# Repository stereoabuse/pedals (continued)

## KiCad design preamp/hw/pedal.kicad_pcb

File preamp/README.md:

# preamp

High-gain preamp pedal by stereoabuse. Derived from the Friedman BE-OD circuit (via the public PedalPCB "Thermionic Distortion" schematic), reworked for downtuned rhythm playing and for driving a power-amp input.

This is the single-section version: the boost is built into the preamp's first stage and only works while the preamp is on. The sibling design with a standalone boost is in [../boost-preamp](../boost-preamp). Commands below are run from inside this folder. Untested hardware: the circuit is simulated and the board passes KiCad DRC, but no board has been built yet.

## What it is

| Control | Type | Notes |
|---|---|---|
| Gain | A1M pot | Audio taper, so the sweep is more usable than the stock linear pot |
| Tight | C100K pot | Bass cut before the gain stages, about 75 Hz to 1.7 kHz |
| Presence | C10K pot | Stock BE-OD presence |
| Treble | B100K pot | Stock |
| Mid | B100K pot | New. About +/-13 dB centred near 750 Hz |
| Volume | A10K pot | Low output impedance for power-amp inputs |
| Depth | SPDT on-off-on | Post-distortion low thump: flat, +6 dB, +10 dB around 90 Hz |
| Clip | SPDT on-off-on | Stock soft clip, none (open), single diode pair (saturated) |
| Bypass | 3PDT footswitch | True bypass |
| Boost | 3PDT footswitch | TS-style tightening boost into the first stage, up to +12 dB above 700 Hz |

Inside: gain trim (stock), boost level trim, noise gate threshold trim, and two solder jumpers (18 V or 9 V rail, gate on or off).

Differences from the BE-OD: no Bass knob (Tight and Depth cover it), added Mid, boost, noise gate, clip switch, and an internal charge pump that runs the op-amps at about 16 V from a 9 V supply or battery.

## Ordering from JLCPCB

Files are in [fab/](fab/).

1. Upload `preamp-revA-gerbers.zip`. Settings: 4 layers, 1.6 mm, 82 x 62.5 mm. Layer order is F, In1, In2, B (`.gtl`, `.g1`, `.g2`, `.gbl`).
2. Turn on PCB Assembly, top side.
3. Upload `preamp-revA-bom.csv` and `preamp-revA-cpl.csv`.
4. In the placement preview, check pin 1 on U1 to U6, the two JFETs (Q1, Q2), the diode cathode bars, and the stripe on C20, C27, C28. JLC's rotation convention differs from KiCad's for some packages; the CPL already applies the usual corrections, but this is the step to catch a mistake.

38 BOM lines, 120 placements. 7 of the lines are JLC "extended" parts (a small one-time fee each). Stock was checked on 2026-11-11.

## Parts you solder

| Part | Qty | Notes |
|---|---|---|
| Alpha 16 mm right-angle PCB pot (RV16AF-41) | 6 | A1M, C100K, C10K, B100K x2, A10K |
| Mini toggle, SPDT on-off-on | 2 | Solder lug or PC pin, 4.7 mm lug pitch |
| 3PDT footswitch | 2 | Wired, not board mounted |
| 3 mm LED | 2 | Any colour |
| 1/4" jack | 2 | Input must be stereo (battery switching) |
| 2.1 mm DC jack with switch lug | 1 | Panel mount, insulated |
| 9V battery snap | 1 | |
| Hammond 1590BB enclosure | 1 | |

Pots, toggles and LEDs mount on the back of the board (the side with the pot outlines). Fit them loosely, bolt everything into the drilled enclosure, then solder, so the heights settle correctly.

Drill template (front view, 1:1): [docs/drill-template-1590BB.svg](docs/drill-template-1590BB.svg). Hole positions in mm from the face centre:

| Hole | x | y | dia |
|---|---|---|---|
| Volume | -31.5 | +23.0 | 7.5 |
| Treble | -10.5 | +23.0 | 7.5 |
| Presence | +10.5 | +23.0 | 7.5 |
| Gain | +31.5 | +23.0 | 7.5 |
| Depth | -8.0 | +1.5 | 6.5 |
| Clip | +8.0 | +1.5 | 6.5 |
| Mid | -31.5 | -8.0 | 7.5 |
| Tight | +31.5 | -8.0 | 7.5 |
| Boost LED | -19.5 | -24.0 | 3.2 |
| Bypass LED | +19.5 | -24.0 | 3.2 |
| Boost switch | -27.0 | -43.0 | 12.5 |
| Bypass switch | +27.0 | -43.0 | 12.5 |

The toggles sit sideways (levers move left and right). The battery lies between the footswitches in the board's notch. That fit is snug: check it with a real battery before drilling.

## Wiring

The diagram ([SVG](docs/wiring.svg)) shows every off-board wire. The tables below list the same connections lug by lug.

Pads are labelled on the SMD side. Looking at the SMD side, the left leg (IN, G, L1) is next to the bypass switch.

Bypass switch (3PDT, columns A B C, row 2 is the common):

| Lug | Goes to |
|---|---|
| A1 | board IN |
| A2 | input jack tip |
| A3 | wire to B3 |
| B1 | board OUT |
| B2 | output jack tip |
| C1 | board L1 (left leg) |
| C2 | board G |
| C3 | board IN (grounds the input when bypassed) |

Boost switch:

| Lug | Goes to |
|---|---|
| A2 | board BST |
| A3 | board G |
| B1 | board L1 (right leg) |
| B2 | board L2 |

The boost is on when BST is left open and off when BST is grounded. Wired as above, the boost LED only lights when the pedal is engaged.

Power: DC jack centre pin to G, DC jack sleeve to +9V, battery red to the DC jack switch lug, battery black to the input jack ring lug, input jack sleeve to G.

Use a regulated 9 V centre-negative supply only. The charge pump chip is rated to 12 V, and there is no over-voltage clamp.

## Setting the trimmers

- GAIN TRIM: sets how hard the last gain stage is driven. Start at halfway.
- BST LVL: boost amount and voicing. One end is a tight mid/treble push (+12 dB above 700 Hz), the other a very mild full-range lift (+1 dB). Most of the useful range is in the first quarter of the turn.
- GATE: threshold. Turn until hiss cuts off when you mute the strings but sustained notes do not chop.

Toggle positions as designed (seen from the front): Clip lever left is stock, centre is open, right is saturated. Depth lever left is medium, centre is flat, right is deep. If a switch you buy works the other way round, turn it 180 degrees.

## If something misbehaves

- Gate causes trouble: cut the GATE solder jumper. The gate is then out of circuit.
- Whine from the charge pump: cut the 18V side of the 18V/9V jumper and bridge the 9V side. If you run on the 9 V rail, also cut the GATE jumper, because the gate needs the higher rail to switch cleanly.
- Test pads: VCC should read about 16 V, VREF about half that, 9V about 8.7 V.

## How the board was made

Everything is generated from [hw/design.py](hw/design.py), which holds the full netlist with JLC part numbers.

## Schematic

[docs/schematic.pdf](docs/schematic.pdf), five sheets. It is drawn by `hw/schematic.py`, which extracts the connectivity of the drawing and refuses to write it unless every pin matches the board netlist, so the drawing and the board cannot drift apart. It is a drawing, not a KiCad schematic file.

| Sheet | Contents |
|---|---|
| [1](docs/schematic-1.png) | Power, voltage doubler, VREF, indicator LEDs |
| [2](docs/schematic-2.png) | Input stage, boost, Tight, gain stage |
| [3](docs/schematic-3.png) | Clip stage, gain trim, Presence, hard clip, gate switch |
| [4](docs/schematic-4.png) | Treble, Depth, Mid, output |
| [5](docs/schematic-5.png) | Noise gate sidechain |

Regenerate with `uv run --with matplotlib python3 hw/schematic.py`.

## Scripts

| Step | Script |
|---|---|
| Simulate the netlist in ngspice | `sim/from_design.py` |
| Draw and verify the schematic | `hw/schematic.py` |
| Place parts | `hw/place.py` |
| Build the KiCad board | `hw/build_pcb.py` |
| Route (own grid router) | `hw/route.py` |
| Apply tracks, fill planes, DRC | `hw/apply_routes.py`, `hw/drc.sh` |
| Gerbers, BOM, CPL, renders | `hw/export.py` |

`hw/make.sh` runs place through DRC. The board file is [hw/pedal.kicad_pcb](hw/pedal.kicad_pcb). Part positions with reference designators: [docs/assembly-smd-side.pdf](docs/assembly-smd-side.pdf).

## Things to check before paying

1. Open `hw/pedal.kicad_pcb` in KiCad and look it over.
2. Pot footprint: 3 pins at 5.0 mm pitch, 16 mm below the shaft, taken from the Alpha RV16AF-41 drawing. Confirm against the pots you buy.
3. Toggle lug pitch (4.7 mm) against the switches you buy.
4. Battery fit in the 1590BB.
5. The routing was done by a simple autorouter. It passes DRC with zero violations and the input stage is kept well away from the high-level nodes, but a high-gain layout can still squeal at maximum gain. The Gain Trim is the first thing to back off if it does.

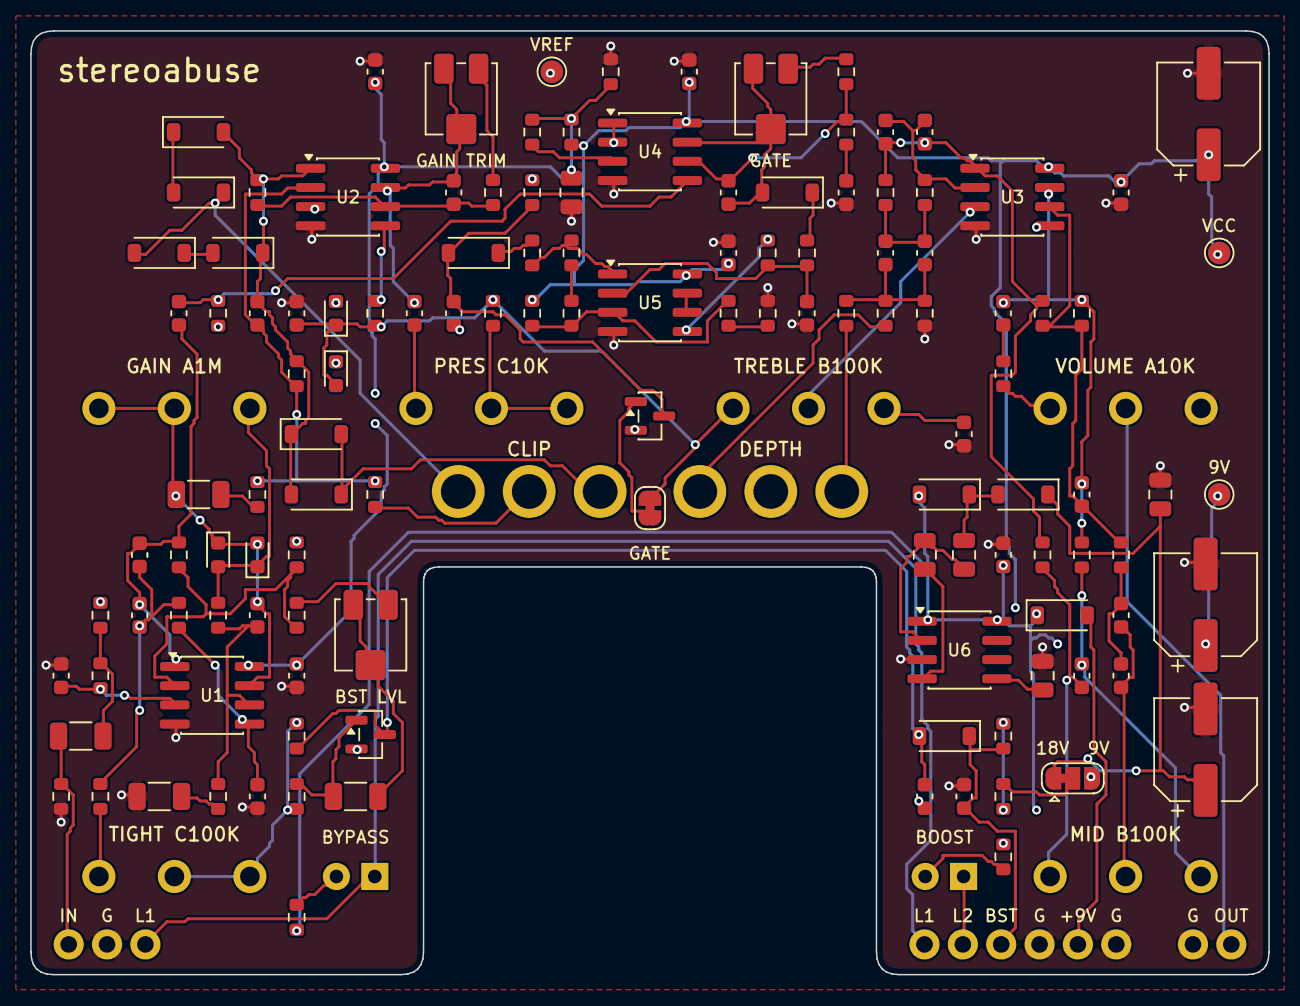
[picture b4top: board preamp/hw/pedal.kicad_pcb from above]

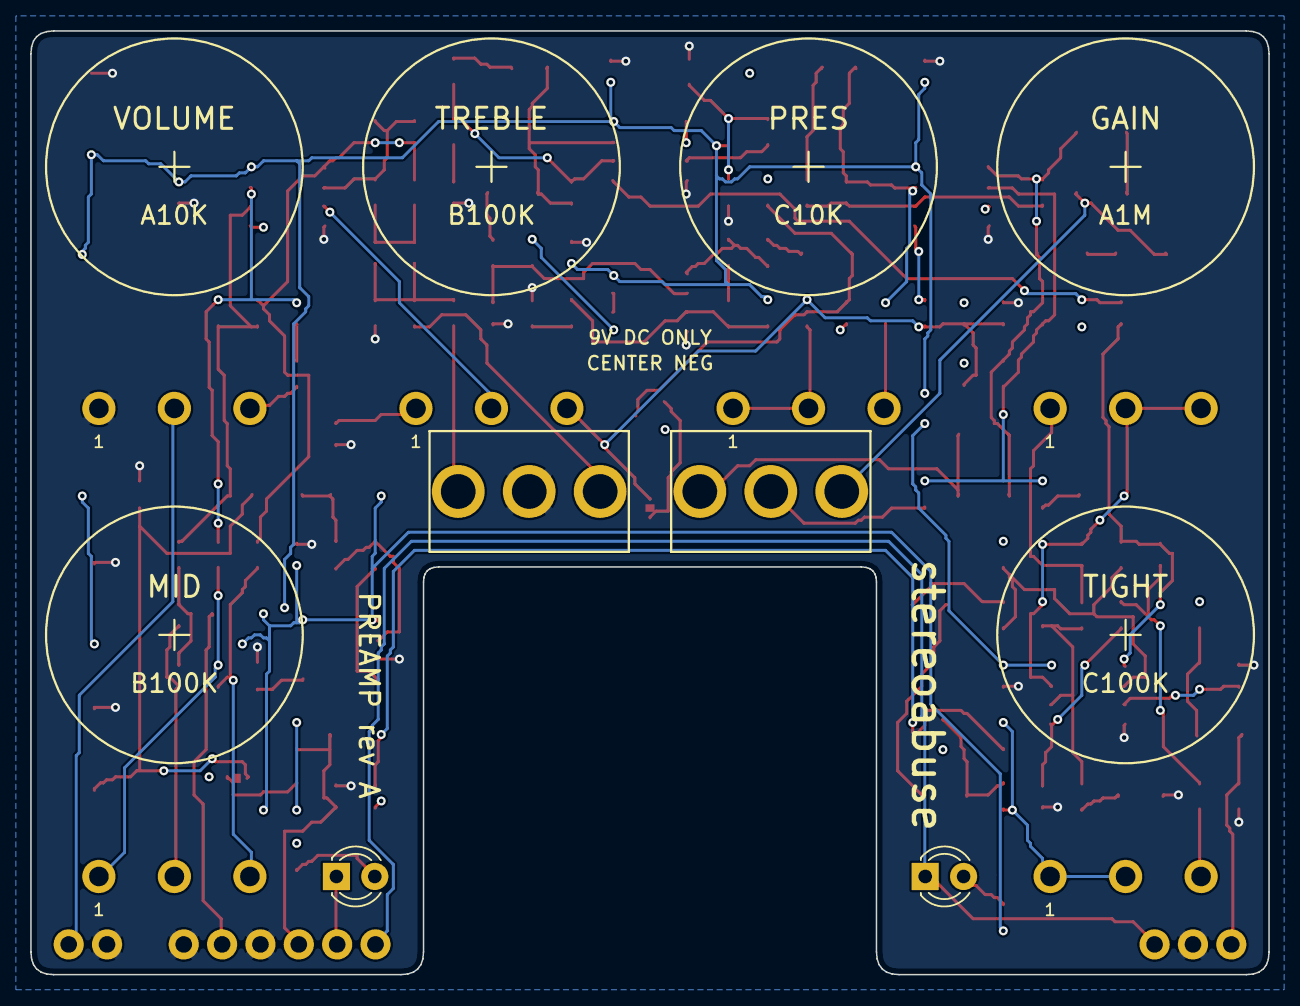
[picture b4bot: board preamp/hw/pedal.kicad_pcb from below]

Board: 4 copper layers, 82.0 x 62.5 mm, 146 parts (2 on the bottom side), 80 nets.

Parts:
C1, C11, C40: 47n NP0; C_1206_3216Metric
C2, C9, C52: 47p; C_0603_1608Metric
C3A, C3B, C14, C16A, C51A: 10n NP0; C_0603_1608Metric
C4: 1n; C_0603_1608Metric
C6, C7, C10, C17A, C21, C29, C30, C42: 100n; C_0603_1608Metric
C8: 100n NP0; C_1206_3216Metric
C12, C13, C62: 100p; C_0603_1608Metric
C15, C16B, C51B: 4.7n; C_0603_1608Metric
C17B, C41, C65: 47n; C_0603_1608Metric
C18, C19, C61: 1u; C_0603_1608Metric
C20, C27, C28: 100u 35V; CP_Elec_6.3x7.7
C22, C23, C24, C25, C26: 10u; C_0805_2012Metric
C50: 3.3n; C_0603_1608Metric
C60: 22n; C_0603_1608Metric
C63: 470n; C_0603_1608Metric
D1, D2, D3: B5819W; D_SOD-123
D4, D5, D6, D7, D8, D9, D10, D11, D12: 1N4148W; D_SOD-123
JP1: 18V/9V; SolderJumper-3_P1.3mm_Bridged12_RoundedPad1.0x1.5mm
JP2: GATE; SolderJumper-2_P1.3mm_Bridged_RoundedPad1.0x1.5mm
J_9V: +9V
J_BST: BST
J_G1, J_G2, J_G3, J_G4: GND
J_IN: IN
J_L1, J_L1B: L1
J_L2: L2
J_OUT: OUT
LED1, LED2, LED3, LED4: RED; LED_0603_1608Metric
LED5: BYPASS; LED_D3.0mm
LED6: BOOST; LED_D3.0mm
Q1, Q2: MMBF4393; SOT-23
R1, R25, R41, R42, R68A, R68B, R70: 1M; R_0603_1608Metric
R2, R24: 470k; R_0603_1608Metric
R3, R8, R14, R15, R32, R33, R50, R51, R61, R67: 10k; R_0603_1608Metric
R4, R9, R10, R11, R12, R22, R69: 22k; R_0603_1608Metric
R5: 39k; R_0603_1608Metric
R7, R40: 4.7k; R_0603_1608Metric
R13: 220k; R_0603_1608Metric
R18, R34, R52: 2.2k; R_0603_1608Metric
R19, R20: 33k; R_0603_1608Metric
R21, R62, R64: 1k; R_0603_1608Metric
R23: 6.8k; R_0603_1608Metric
R30: 22R; R_0603_1608Metric
R43, R53, R54, R60, R65, R66: 100k; R_0603_1608Metric
R63: 150k; R_0603_1608Metric
R71, R72: 3.3k; R_0603_1608Metric
RV1: C100K TIGHT
RV2: A1M GAIN
RV3: C10K PRES
RV4: B100K TREBLE
RV5: B100K MID
RV6: A10K VOLUME
RV7, RV8, RV9: 100k; Potentiometer_Bourns_3314J_Vertical
SW1: CLIP
SW2: DEPTH
TP1: VCC; TestPoint_Pad_D1.5mm
TP2: VREF; TestPoint_Pad_D1.5mm
TP3: 9V; TestPoint_Pad_D1.5mm
U1, U2, U3, U4: TL072; SOIC-8_3.9x4.9mm_P1.27mm
U5: LM358; SOIC-8_3.9x4.9mm_P1.27mm
U6: TC7660S; SOIC-8_3.9x4.9mm_P1.27mm

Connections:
BC: C42.1, D12.1, J_BST.1, R43.1
BG: C41.1, D12.2, Q2.3, R42.1
BQ: C40.2, Q2.1, R41.1
BX: R40.2, RV7.1
BY: C40.1, RV7.2, RV7.3
CLA: D4.2, D7.1, SW1.1
CLB: D8.2, D9.1, SW1.3
CMP: R68A.1, R69.1, U5.1
CN: C22.2, U6.4
CP: C22.1, C24.2, U6.2
CX: C24.1, D2.1, D3.2
D45: D4.1, D5.2
D67: D6.1, D7.2
DPA: R22.2, SW2.1
DPB: R23.2, SW2.3
ENV: C63.1, R63.1, R64.2, U5.2
GND: C2.2, C4.2, C6.2, C7.2, C8.2, C10.2, C14.2, C15.2, C20.2, C21.2, C23.1, C25.2, C26.2, C27.2, C28.2, C29.2, C30.2, C42.2, C61.2, C63.2, J_G1.1, J_G2.1, J_G3.1, J_G4.1, R1.2, R25.2, R33.2, R67.2, RV6.1, SW2.2, U1.4, U2.4, U3.4, U4.4, U5.4, U6.3
IN: C1.1, J_IN.1, R1.1
L1: J_L1.1, J_L1B.1, LED5.1
L2: J_L2.1, LED6.1
LA1: LED5.2, R71.2
LA2: LED6.2, R72.2
MA: C50.1, R50.2, RV5.3
MB: C50.2, R51.2, RV5.1
MW: C51A.1, C51B.1, RV5.2
MX: C51A.2, C51B.2, R52.1
N9: C8.1, R9.2
N11: C11.2, R11.1
N61: R61.2, RV9.1
N62: C61.1, R62.2
N64: D10.1, R64.1
N66: R66.2, R67.1
N68: R68A.2, R68B.1
N69: D11.1, R69.2
NA: C1.2, R2.1, R3.1
NB: C3A.2, C3B.2, R7.1, R8.1
ND: R12.2, SW1.2
NDP: C17A.2, C17B.2, R22.1, R23.1, R25.1
NG: LED1.2, LED2.1, R10.2, RV2.1
NGATE: C65.1, D11.2, Q1.3, R70.1
NH: C14.1, JP2.2, LED3.2, LED4.1, R18.2, R24.1, RV4.3
NM: C17A.1, C17B.1, R19.2, R20.1
NO: C18.2, R21.1
NP: R18.1, RV3.1, RV3.2
NREF: R65.2, R66.1, R68B.2, U5.3
NS: C60.2, R60.1, U4.5
NT: R7.2, RV1.3
NTR: R15.2, RV8.1
OUT: J_OUT.1, RV6.2
QD: JP2.1, Q1.1
S1: C3A.1, C3B.1, C60.1, R5.2, U1.1
S2: C9.2, C11.1, LED1.1, LED2.2, RV2.2, RV2.3, U1.7
S3: C12.2, D5.1, D6.2, D8.1, D9.2, R13.2, R14.1, U2.1
S4: C13.2, C19.1, RV8.2, RV8.3, U2.7
S4C: C19.2, RV3.3
S5: C16A.2, C16B.2, R20.2, R50.1, R53.1, U3.1
S6: C18.1, C52.2, R51.1, R54.2, U3.7
SG: C62.2, D10.2, RV9.2, RV9.3, U4.7
SPARE: U5.6, U5.7
T1: C15.1, RV4.1
TW: RV4.2, U3.3
U1AN: R4.1, R5.1, R40.1, U1.2
U1AP: C2.1, R3.2, U1.3
U1BN: C9.1, R9.1, R10.1, U1.6
U1BP: C4.1, R8.2, U1.5
U2AN: C12.1, R11.2, R12.1, R13.1, U2.2
U2BN: C13.1, R14.2, R15.1, U2.6
U3AN: C16A.1, C16B.1, R19.1, U3.2
U3BN: C52.1, R52.2, R53.2, R54.1, U3.6
U4BN: C62.1, R61.1, R62.1, U4.6
V3: R21.2, RV6.3
V9: C20.1, C21.1, D1.1, D2.2, JP1.3, R71.1, R72.1, TP3.1, U6.1, U6.8
V18: C26.1, C27.1, D3.1, JP1.1
VB: C25.1, R32.2, R33.1, R34.1
VBF: R34.2, U4.3
VCC: C6.1, C7.1, C10.1, C28.1, C29.1, C30.1, R30.2, R32.1, R43.2, R65.1, TP1.1, U1.8, U2.8, U3.8, U4.8, U5.8
VIN: D1.2, J_9V.1
VNEG: C23.2, U6.5
VREF: C41.2, C65.2, LED3.1, LED4.2, Q1.2, Q2.2, R2.2, R4.2, R24.2, R41.2, R42.2, R60.2, R63.2, R70.2, RV1.1, RV1.2, TP2.1, U2.3, U2.5, U3.5, U4.1, U4.2, U5.5
VSEL: JP1.2, R30.1

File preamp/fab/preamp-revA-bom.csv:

Comment,Designator,Footprint,LCSC Part #
47n NP0,"C1,C11,C40",C_1206_3216Metric,C5451690
100p,"C12,C13,C62",C_0603_1608Metric,C14858
4.7n,"C15,C16B,C51B",C_0603_1608Metric,C53987
1u,"C18,C19,C61",C_0603_1608Metric,C15849
47p,"C2,C9,C52",C_0603_1608Metric,C1671
100u 35V,"C20,C27,C28",CP_Elec_6.3x7.7,C2836442
100n,"C6,C7,C10,C17A,C21,C29,C30,C42",C_0603_1608Metric,C14663
10u,"C22,C23,C24,C25,C26",C_0805_2012Metric,C15850
10n NP0,"C3A,C3B,C14,C16A,C51A",C_0603_1608Metric,C2894187
1n,C4,C_0603_1608Metric,C1588
47n,"C17B,C41,C65",C_0603_1608Metric,C1622
3.3n,C50,C_0603_1608Metric,C1613
22n,C60,C_0603_1608Metric,C21122
470n,C63,C_0603_1608Metric,C1623
100n NP0,C8,C_1206_3216Metric,C170182
B5819W,"D1,D2,D3",D_SOD-123,C8598
1N4148W,"D4,D5,D6,D7,D8,D9,D10,D11,D12",D_SOD-123,C81598
RED,"LED1,LED2,LED3,LED4",LED_0603_1608Metric,C2286
MMBF4393,"Q1,Q2",SOT-23,C152291
1M,"R1,R25,R41,R42,R68A,R68B,R70",R_0603_1608Metric,C22935
220k,R13,R_0603_1608Metric,C22961
33k,"R19,R20",R_0603_1608Metric,C4216
470k,"R2,R24",R_0603_1608Metric,C23178
1k,"R21,R62,R64",R_0603_1608Metric,C21190
6.8k,R23,R_0603_1608Metric,C23212
22R,R30,R_0603_1608Metric,C23345
10k,"R3,R8,R14,R15,R32,R33,R50,R51,R61,R67",R_0603_1608Metric,C25804
2.2k,"R18,R34,R52",R_0603_1608Metric,C4190
22k,"R4,R9,R10,R11,R12,R22,R69",R_0603_1608Metric,C31850
4.7k,"R7,R40",R_0603_1608Metric,C23162
100k,"R43,R53,R54,R60,R65,R66",R_0603_1608Metric,C25803
39k,R5,R_0603_1608Metric,C23153
150k,R63,R_0603_1608Metric,C22807
3.3k,"R71,R72",R_0603_1608Metric,C22978
100k,"RV7,RV8,RV9",Potentiometer_Bourns_3314J_Vertical,C51284
TL072,"U1,U2,U3,U4",SOIC-8_3.9x4.9mm_P1.27mm,C6961
LM358,U5,SOIC-8_3.9x4.9mm_P1.27mm,C7950
TC7660S,U6,SOIC-8_3.9x4.9mm_P1.27mm,C636973

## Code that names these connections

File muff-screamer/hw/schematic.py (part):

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                    "YSA   W while the Muff is on, else TSO\n"
                    "OSEL  YSA while the Screamer is on, else XMF.  OSEL feeds the output buffer.")
    # mixer
    s.label(4, 108, "TSO", "l"); s.w((4, 108), (8, 108)); s.R("R80", 11, 108, "r")
    s.label(4, 114, "MFO", "l"); s.w((4, 114), (8, 114)); s.R("R81", 11, 114, "r"); s.w((14, 108), (14, 114)); s.w((14, 112), (22, 112))
    s.opamp("U3", "B", 27, 110, plus_top=True); s.w((22, 108), (20, 108), (20, 104)); s.flag(20, 104, "VREF")
    s.w((18, 112), (18, 118), (22, 118)); s.R("R82", 25, 118, "r"); s.w((28, 118), (34, 118), (34, 110), (32, 110))
    s.w((18, 118), (18, 123), (23, 123)); s.C("C80", 25, 123, "r"); s.w((27, 123), (34, 123), (34, 118))
    s.w((34, 110), (38, 110)); s.label(38, 110, "MIX", "r")
    # output buffer
    s.label(60, 108, "OSEL", "l"); s.w((60, 108), (70, 108)); s.w((65, 108), (65, 105)); s.R("R83", 65, 102, "d"); s.flag(65, 99, "VREF")
    s.opamp("U4", "B", 75, 110, plus_top=True); s.w((70, 112), (68, 112), (68, 116), (82, 116), (82, 110), (80, 110))
    s.w((82, 110), (85, 110)); s.C("C81", 87, 110, "r"); s.w((89, 110), (91, 110)); s.R("R85", 94, 110, "r"); s.w((97, 110), (105, 110))
    s.w((101, 110), (101, 111)); s.R("R86", 101, 114, "d"); s.gnd(101, 117); s.pad("J_OUT", 105, 110, "r")
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    # order toggle
    s.sw("SW1", 120, 146, "r", (-3, -7, "on-off-on", "center")); s.w((117, 146), (115, 146)); s.gnd(115, 146)
    s.w((123, 144), (123, 140), (150, 140)); s.w((130, 139), (130, 140)); s.R("R96", 130, 136, "d"); s.flag(130, 133, "VCC")
    s.w((138, 140), (138, 141)); s.C("C92", 138, 143, "d"); s.gnd(138, 145); s.label(150, 140, "NAB", "r", "low = Screamer > Muff")
    s.w((123, 148), (123, 152), (150, 152)); s.w((130, 152), (130, 153)); s.R("R97", 130, 156, "d"); s.flag(130, 159, "VCC", "d")
    s.w((138, 152), (138, 153)); s.C("C93", 138, 155, "d"); s.gnd(138, 157); s.label(150, 152, "NBA", "r", "low = Muff > Screamer")
    return s


def sheet_screamer():
    s = Sheet("Screamer: TS808 circuit (TSI in, TSO out)")
    s.label(4, 42, "TSI", "l"); s.w((4, 42), (12, 42)); s.w((8, 42), (8, 43)); s.R("R41", 8, 46, "d"); s.flag(8, 49, "VREF", "d")
    s.C("C40", 14, 42, "r"); s.w((16, 42), (26, 42)); s.w((21, 42), (21, 41)); s.R("R40", 21, 38, "d"); s.flag(21, 35, "VREF")
    s.opamp("U2", "A", 31, 44, plus_top=True)
    s.w((26, 46), (24, 46), (24, 67)); s.w((36, 44), (40, 44)); s.w((40, 44), (40, 64))
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    # level
    s.w((76, 46), (80, 46)); s.C("C45", 82, 46, "r"); s.w((84, 46), (90, 46), (90, 48)); s.pot("RV3", 90, 51, "d", "3", -1); s.flag(90, 54, "VREF", "d")
    s.w((92, 51), (98, 51)); s.opamp("U3", "A", 103, 53, plus_top=True)
    s.w((98, 55), (96, 55), (96, 59), (110, 59), (110, 53), (108, 53)); s.w((110, 53), (114, 53)); s.label(114, 53, "TSO", "r")
    s.note(4, 84, "Stock TS808 values. Clipping stage: gain 1 + (R43 + Drive) / R42 above 720 Hz (R42 with C41), soft-clipped by D2/D3.\n"
                  "The original's transistor buffers are not needed: the pedal's input buffer (or the Muff's output buffer) drives TSI,\n"
                  "and U3A buffers the Level pot. Two parts differ from the original: C42 is 47p (51p) and the bias resistor R40 is 100k (10k),\n"
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    s.flag(4, 8, "VCC"); s.w((4, 8), (8, 8)); s.R("R73", 11, 8, "r"); s.w((14, 8), (26, 8)); s.w((20, 8), (20, 9)); s.C("C64", 20, 11, "d"); s.gnd(20, 13)
    s.flag(26, 8, "VM")
    # input stage
    s.label(4, 40, "MFI", "l"); s.w((4, 40), (10, 40)); s.w((7, 40), (7, 41)); s.R("R84", 7, 44, "d"); s.flag(7, 47, "VREF", "d")
    s.C("C50", 12, 42 - 2, "r"); s.w((14, 40), (16, 40)); s.R("R50", 19, 40, "r"); s.w((22, 40), (31, 40)); s.npn("Q1", 34, 40)
    s.w((26, 40), (26, 42)); s.R("R51", 26, 45, "d", ); s.gnd(26, 48); s.R("R54", 34, 46, "d"); s.gnd(34, 49)
    s.w((34, 37), (34, 30)); s.R("R53", 34, 27, "d"); s.flag(34, 24, "VM")
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    s.w((204, 32), (212, 32)); s.C("C62", 214, 32, "r"); s.w((216, 32), (232, 32), (232, 34)); s.pot("RV6", 232, 37, "d", "3", -1); s.gnd(232, 40)
    s.w((234, 37), (238, 37)); s.C("C63", 240, 37, "r"); s.w((242, 37), (252, 37)); s.w((246, 37), (246, 36)); s.R("R72", 246, 33, "d"); s.flag(246, 30, "VREF")
    s.opamp("U4", "A", 257, 39, plus_top=True)
    s.w((252, 41), (250, 41), (250, 45), (264, 45), (264, 39), (262, 39)); s.w((264, 39), (268, 39)); s.label(268, 39, "MFO", "r")
    s.note(4, 58, "Values follow Kit Rae's trace of the V7C/V8 black Russian Big Muff (bigmuffpage.com). BC847C stands in for the BC547C.\n"
                  "R73/C64 give the Muff its own filtered supply. U4A buffers the Volume pot so the routing switches see a low impedance.")
    return s
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
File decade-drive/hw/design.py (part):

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R39   R    1M      N1 V1
C26   C    1n_NP0  N1 V1
R40   R    270k    V3 N1
SW14  SW   PITCH_3 PU3 N1 PD3
R41   R    91k     PU3 V3
C27   C    1n_NP0  PD3 V1
C28   C    1n_NP0  PD3 V1
C29   C    1n_NP0  PD3 V1
R42   R    10M     PD3 VREF
R43   R    270k    V1 N2
C30   C    1n_NP0  N2 V2
SW15  SW   PITCH_1 PU1 N2 PD1
R44   R    680k    PU1 V1
C31   C    330p    PD1 V2
C32   C    330p    PD1 V2
C33   C    100p    PD1 V2
R45   R    10M     PD1 VREF
R46   R    120k    V2 N3
R47   R    68k     N3 TN
RV3   RV   100k    TN V3 V3
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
